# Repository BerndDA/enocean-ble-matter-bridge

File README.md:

# Matter-over-Thread Gateways (BLE, EnOcean and Nuki)

Firmware and hardware for nRF52840 gateways that bring existing devices into a Matter smart home over Thread. There are three separate apps, built from a shared bridge core:

- **BLE gateway** ([firmware/ble-gateway/](firmware/ble-gateway/)): BLE temperature/humidity sensors (BTHome) and eQ-3 radiator thermostats.
- **EnOcean gateway** ([firmware/enocean-gateway/](firmware/enocean-gateway/)): Eltako and D2-01 actuators through a TCM 310/515 module.
- **Nuki gateway** ([firmware/nuki-gateway/](firmware/nuki-gateway/)): a Nuki Smart Lock (3rd/4th generation) over Bluetooth LE, as two Matter door locks: "Front door" and "Door opener".

All are based on the nRF Connect SDK Matter Bridge application (pinned to v3.4.2) and are meant for home use, not certification.

**Documentation is in the [wiki](https://github.com/BerndDA/enocean-ble-matter-bridge/wiki)**:

- [Ready-made firmware](https://github.com/BerndDA/enocean-ble-matter-bridge/wiki/Ready-Made-Firmware) and [commissioning](https://github.com/BerndDA/enocean-ble-matter-bridge/wiki/Commissioning)
- [BLE gateway](https://github.com/BerndDA/enocean-ble-matter-bridge/wiki/BLE-Gateway), [EnOcean gateway](https://github.com/BerndDA/enocean-ble-matter-bridge/wiki/EnOcean-Gateway) and its [commands](https://github.com/BerndDA/enocean-ble-matter-bridge/wiki/EnOcean-Gateway-Commands), [Nuki gateway](https://github.com/BerndDA/enocean-ble-matter-bridge/wiki/Nuki-Gateway)
- Hardware: [boards](https://github.com/BerndDA/enocean-ble-matter-bridge/wiki/Boards), [EnMT carrier board](https://github.com/BerndDA/enocean-ble-matter-bridge/wiki/EnMT-Carrier-Board), [EnOcean bridge PCB](https://github.com/BerndDA/enocean-ble-matter-bridge/wiki/EnOcean-Bridge-PCB), [bootloader](https://github.com/BerndDA/enocean-ble-matter-bridge/wiki/Bootloader)
- Development: [toolchain setup](https://github.com/BerndDA/enocean-ble-matter-bridge/wiki/Toolchain-Setup), [building and flashing](https://github.com/BerndDA/enocean-ble-matter-bridge/wiki/Building-and-Flashing), [repository layout](https://github.com/BerndDA/enocean-ble-matter-bridge/wiki/Repository-Layout), [measurements](https://github.com/BerndDA/enocean-ble-matter-bridge/wiki/Measurements)

Quick start on an nRF52840 DK with the SDK installed:

```sh
make flash                         # BLE gateway; APP=enocean-gateway or APP=nuki-gateway for the others
make identity                      # the board's Matter setup code
```

`make` lists all targets. Open tasks are in [TODO.md](TODO.md).

The wiki is also a git submodule in [wiki/](wiki/): `git submodule update --init wiki` checks it out for editing next to the code. Commit and push page changes inside `wiki/` (that publishes them), then commit the new `wiki` pointer here; `git submodule update --remote wiki` fetches edits made in the browser.

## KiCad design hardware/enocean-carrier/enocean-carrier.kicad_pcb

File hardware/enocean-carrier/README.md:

# EnOcean carrier board (EnMT)

A Pro Micro nRF52840 (nice!nano) on a 2-layer carrier with a TCM 515, hand-soldered.

KiCad project, fabrication files (`fab/`), 3D-printed case (`case/`) and the generator scripts (`tools/`). Design, decisions, ordering and bring-up are on the wiki page [EnMT Carrier Board](https://github.com/BerndDA/enocean-ble-matter-bridge/wiki/EnMT-Carrier-Board).

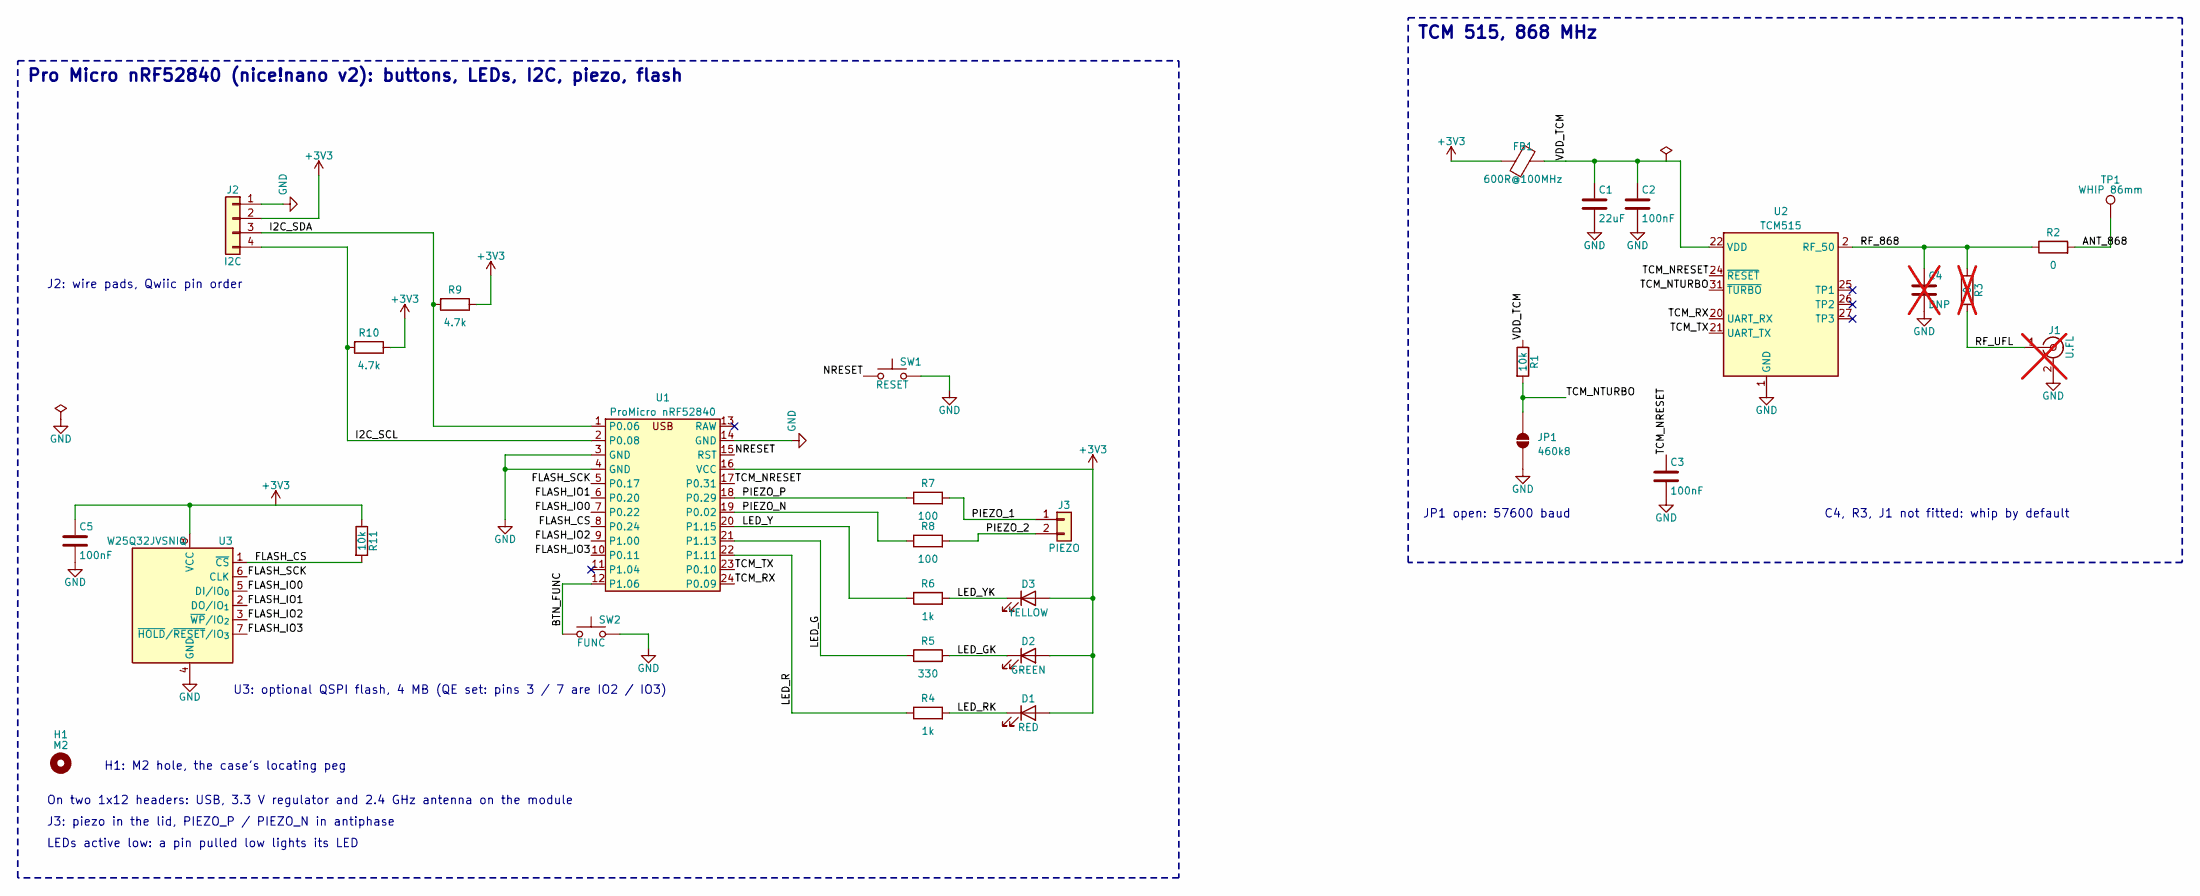
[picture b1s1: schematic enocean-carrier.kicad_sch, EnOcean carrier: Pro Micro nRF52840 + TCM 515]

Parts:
C1: 22uF; C_0805_2012Metric_Pad1.18x1.45mm_HandSolder; MPN CL21A226MAQNNNE; LCSC C45783
C2, C3: 100nF; C_0805_2012Metric_Pad1.18x1.45mm_HandSolder; MPN CC0805KRX7R9BB104; LCSC C49678
C4: DNP; C_0805_2012Metric_Pad1.18x1.45mm_HandSolder; not fitted
C5: 100nF; C_0603_1608Metric_Pad1.08x0.95mm_HandSolder; MPN CC0603KRX7R9BB104; LCSC C14663
D1: RED; LED_0805_2012Metric; MPN NCD0805R1; LCSC C84256
D2: GREEN; LED_0805_2012Metric; MPN KT-0805G; LCSC C2297
D3: YELLOW; LED_0805_2012Metric; MPN KT-0805Y; LCSC C2296
FB1: 600R@100MHz; L_0805_2012Metric_Pad1.05x1.20mm_HandSolder; MPN GZ2012D601TF; LCSC C1017
H1: M2; MountingHole_2.2mm_M2
J1: U.FL; U.FL_Hirose_U.FL-R-SMT-1_Vertical; MPN U.FL-R-SMT-1(80); LCSC C88374; not fitted
J2: I2C; WirePads_1x04_P2.54mm_Drill0.9mm
J3: PIEZO; WirePads_1x02_P2.54mm_Drill0.9mm
JP1: 460k8; SolderJumper-2_P1.3mm_Open_RoundedPad1.0x1.5mm
R1: 10k; R_0805_2012Metric_Pad1.20x1.40mm_HandSolder; MPN 0805W8F1002T5E; LCSC C17414
R2: 0; R_0805_2012Metric_Pad1.20x1.40mm_HandSolder; MPN 0805W8F0000T5E; LCSC C17477
R3: 0; R_0805_2012Metric_Pad1.20x1.40mm_HandSolder; MPN 0805W8F0000T5E; LCSC C17477; not fitted
R4, R6: 1k; R_0603_1608Metric_Pad0.98x0.95mm_HandSolder; MPN 0603WAF1001T5E; LCSC C21190
R5: 330; R_0603_1608Metric_Pad0.98x0.95mm_HandSolder; MPN 0603WAF3300T5E; LCSC C23138
R7, R8: 100; R_0603_1608Metric_Pad0.98x0.95mm_HandSolder; MPN 0603WAF1000T5E; LCSC C22775
R9, R10: 4.7k; R_0603_1608Metric_Pad0.98x0.95mm_HandSolder; MPN 0603WAF4701T5E; LCSC C23162
R11: 10k; R_0603_1608Metric_Pad0.98x0.95mm_HandSolder; MPN 0603WAF1002T5E; LCSC C25804
SW1: RESET; SW_Push_1P1T_XKB_TS-1187A; MPN TS-1187A-B-A-B; LCSC C318884
SW2: FUNC; SW_Push_1P1T_XKB_TS-1187A; MPN TS-1187A-B-A-B; LCSC C318884
TP1: WHIP 86mm; WhipPad_D3.2mm_Drill1.8mm
U1: ProMicro nRF52840; ProMicro_nRF52840; MPN nice!nano v2 / SuperMini nRF52840 with 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
U2: TCM515; TCM515_HandSolder; MPN EnOcean TCM 515 (S3003-K515), 868.3 MHz
U3: W25Q32JVSNIQ; SOIC-8_3.9x4.9mm_P1.27mm; MPN W25Q32JVSNIQ; LCSC C5355146

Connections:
+3V3: C5.1, D1.2 (A), D2.2 (A), D3.2 (A), FB1.1, J2.2, R9.1, R10.1, R11.1, U1.16 (VCC), U3.8 (VCC)
/ANT_868: R2.2, TP1.1
/BTN_FUNC: SW2.1, U1.12 (P1.06)
/FLASH_CS: R11.2, U1.8 (P0.24), U3.1 (~CS)
/FLASH_IO0: U1.7 (P0.22), U3.5 (DI/IO_{0})
/FLASH_IO1: U1.6 (P0.20), U3.2 (DO/IO_{1})
/FLASH_IO2: U1.9 (P1.00), U3.3 (~WP/IO_{2})
/FLASH_IO3: U1.10 (P0.11), U3.7 (~HOLD/~RESET/IO_{3})
/FLASH_SCK: U1.5 (P0.17), U3.6 (CLK)
/I2C_SCL: J2.4, R10.2, U1.2 (P0.08)
/I2C_SDA: J2.3, R9.2, U1.1 (P0.06)
/LED_G: R5.1, U1.21 (P1.13)
/LED_GK: D2.1 (K), R5.2
/LED_R: R4.1, U1.22 (P1.11)
/LED_RK: D1.1 (K), R4.2
/LED_Y: R6.1, U1.20 (P1.15)
/LED_YK: D3.1 (K), R6.2
/NRESET: SW1.1, U1.15 (RST)
/PIEZO_1: J3.1, R7.2
/PIEZO_2: J3.2, R8.2
/PIEZO_N: R8.1, U1.19 (P0.02)
/PIEZO_P: R7.1, U1.18 (P0.29)
/RF_868: C4.1, R2.1, R3.1, U2.2 (RF_50)
/RF_UFL: J1.1 (In), R3.2
/TCM_NRESET: C3.1, U1.17 (P0.31), U2.24 (~RESET)
/TCM_NTURBO: JP1.1 (A), R1.2, U2.31 (~TURBO)
/TCM_RX: U1.24 (P0.09), U2.20 (UART_RX)
/TCM_TX: U1.23 (P0.10), U2.21 (UART_TX)
/VDD_TCM: C1.1, C2.1, FB1.2, R1.1, U2.22 (VDD)
GND: C1.2, C2.2, C3.2, C4.2, C5.2, J1.2 (Ext), J2.1, JP1.2 (B), SW1.2, SW2.2, U1.3 (GND), U1.4 (GND), U1.14 (GND), U2.1 (GND), U2.3 (GND), U2.6 (GND), U2.15 (GND), U2.23 (GND), U3.4 (GND)

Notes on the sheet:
Pro Micro nRF52840 (nice!nano v2): buttons, LEDs, I2C, piezo, flash
TCM 515, 868 MHz
J2: wire pads, Qwiic pin order
On two 1x12 headers: USB, 3.3 V regulator and 2.4 GHz antenna on the module
U3: optional QSPI flash, 4 MB (QE set: pins 3 / 7 are IO2 / IO3)
H1: M2 hole, the case's locating peg
J3: piezo in the lid, PIEZO_P / PIEZO_N in antiphase
LEDs active low: a pin pulled low lights its LED
JP1 open: 57600 baud
C4, R3, J1 not fitted: whip by default

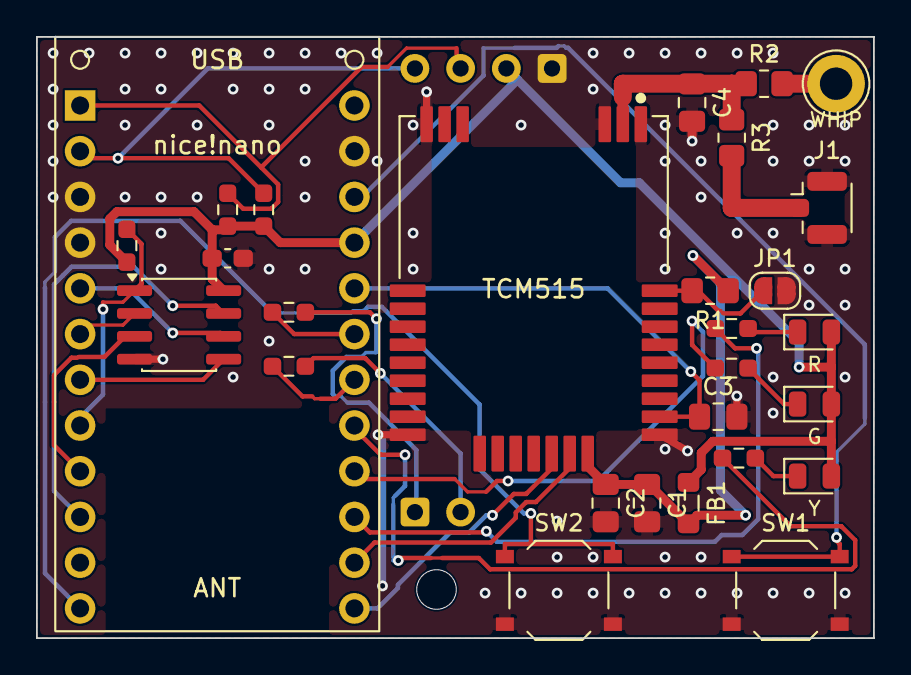
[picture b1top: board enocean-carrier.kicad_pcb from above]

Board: 2 copper layers, 46.5 x 33.4 mm, 31 parts (0 on the bottom side), 30 nets.

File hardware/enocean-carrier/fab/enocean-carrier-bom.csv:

Comment,Designator,Footprint,LCSC Part #
600R@100MHz,FB1,L_0805_2012Metric_Pad1.05x1.20mm_HandSolder,C1017
100nF,C5,C_0603_1608Metric_Pad1.08x0.95mm_HandSolder,C14663
10k,R1,R_0805_2012Metric_Pad1.20x1.40mm_HandSolder,C17414
0,R2,R_0805_2012Metric_Pad1.20x1.40mm_HandSolder,C17477
1k,"R4,R6",R_0603_1608Metric_Pad0.98x0.95mm_HandSolder,C21190
100,"R7,R8",R_0603_1608Metric_Pad0.98x0.95mm_HandSolder,C22775
YELLOW,D3,LED_0805_2012Metric,C2296
GREEN,D2,LED_0805_2012Metric,C2297
330,R5,R_0603_1608Metric_Pad0.98x0.95mm_HandSolder,C23138
4.7k,"R10,R9",R_0603_1608Metric_Pad0.98x0.95mm_HandSolder,C23162
10k,R11,R_0603_1608Metric_Pad0.98x0.95mm_HandSolder,C25804
RESET/FUNC,"SW1,SW2",SW_Push_1P1T_XKB_TS-1187A,C318884
22uF,C1,C_0805_2012Metric_Pad1.18x1.45mm_HandSolder,C45783
100nF,"C2,C3",C_0805_2012Metric_Pad1.18x1.45mm_HandSolder,C49678
W25Q32JVSNIQ,U3,SOIC-8_3.9x4.9mm_P1.27mm,C5355146
RED,D1,LED_0805_2012Metric,C84256

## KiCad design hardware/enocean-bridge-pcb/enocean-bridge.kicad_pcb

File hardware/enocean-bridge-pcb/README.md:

# EnOcean–Matter bridge PCB

One board for the EnOcean gateway: a bare nRF52840, a TCM 515 and USB-C, pin-compatible with the Pro Micro build.

KiCad project, fabrication files (`fab/`), 3D-printed case (`case/`) and the generator scripts (`tools/`). Design, decisions, ordering and bring-up are on the wiki page [EnOcean Bridge PCB](https://github.com/BerndDA/enocean-ble-matter-bridge/wiki/EnOcean-Bridge-PCB).

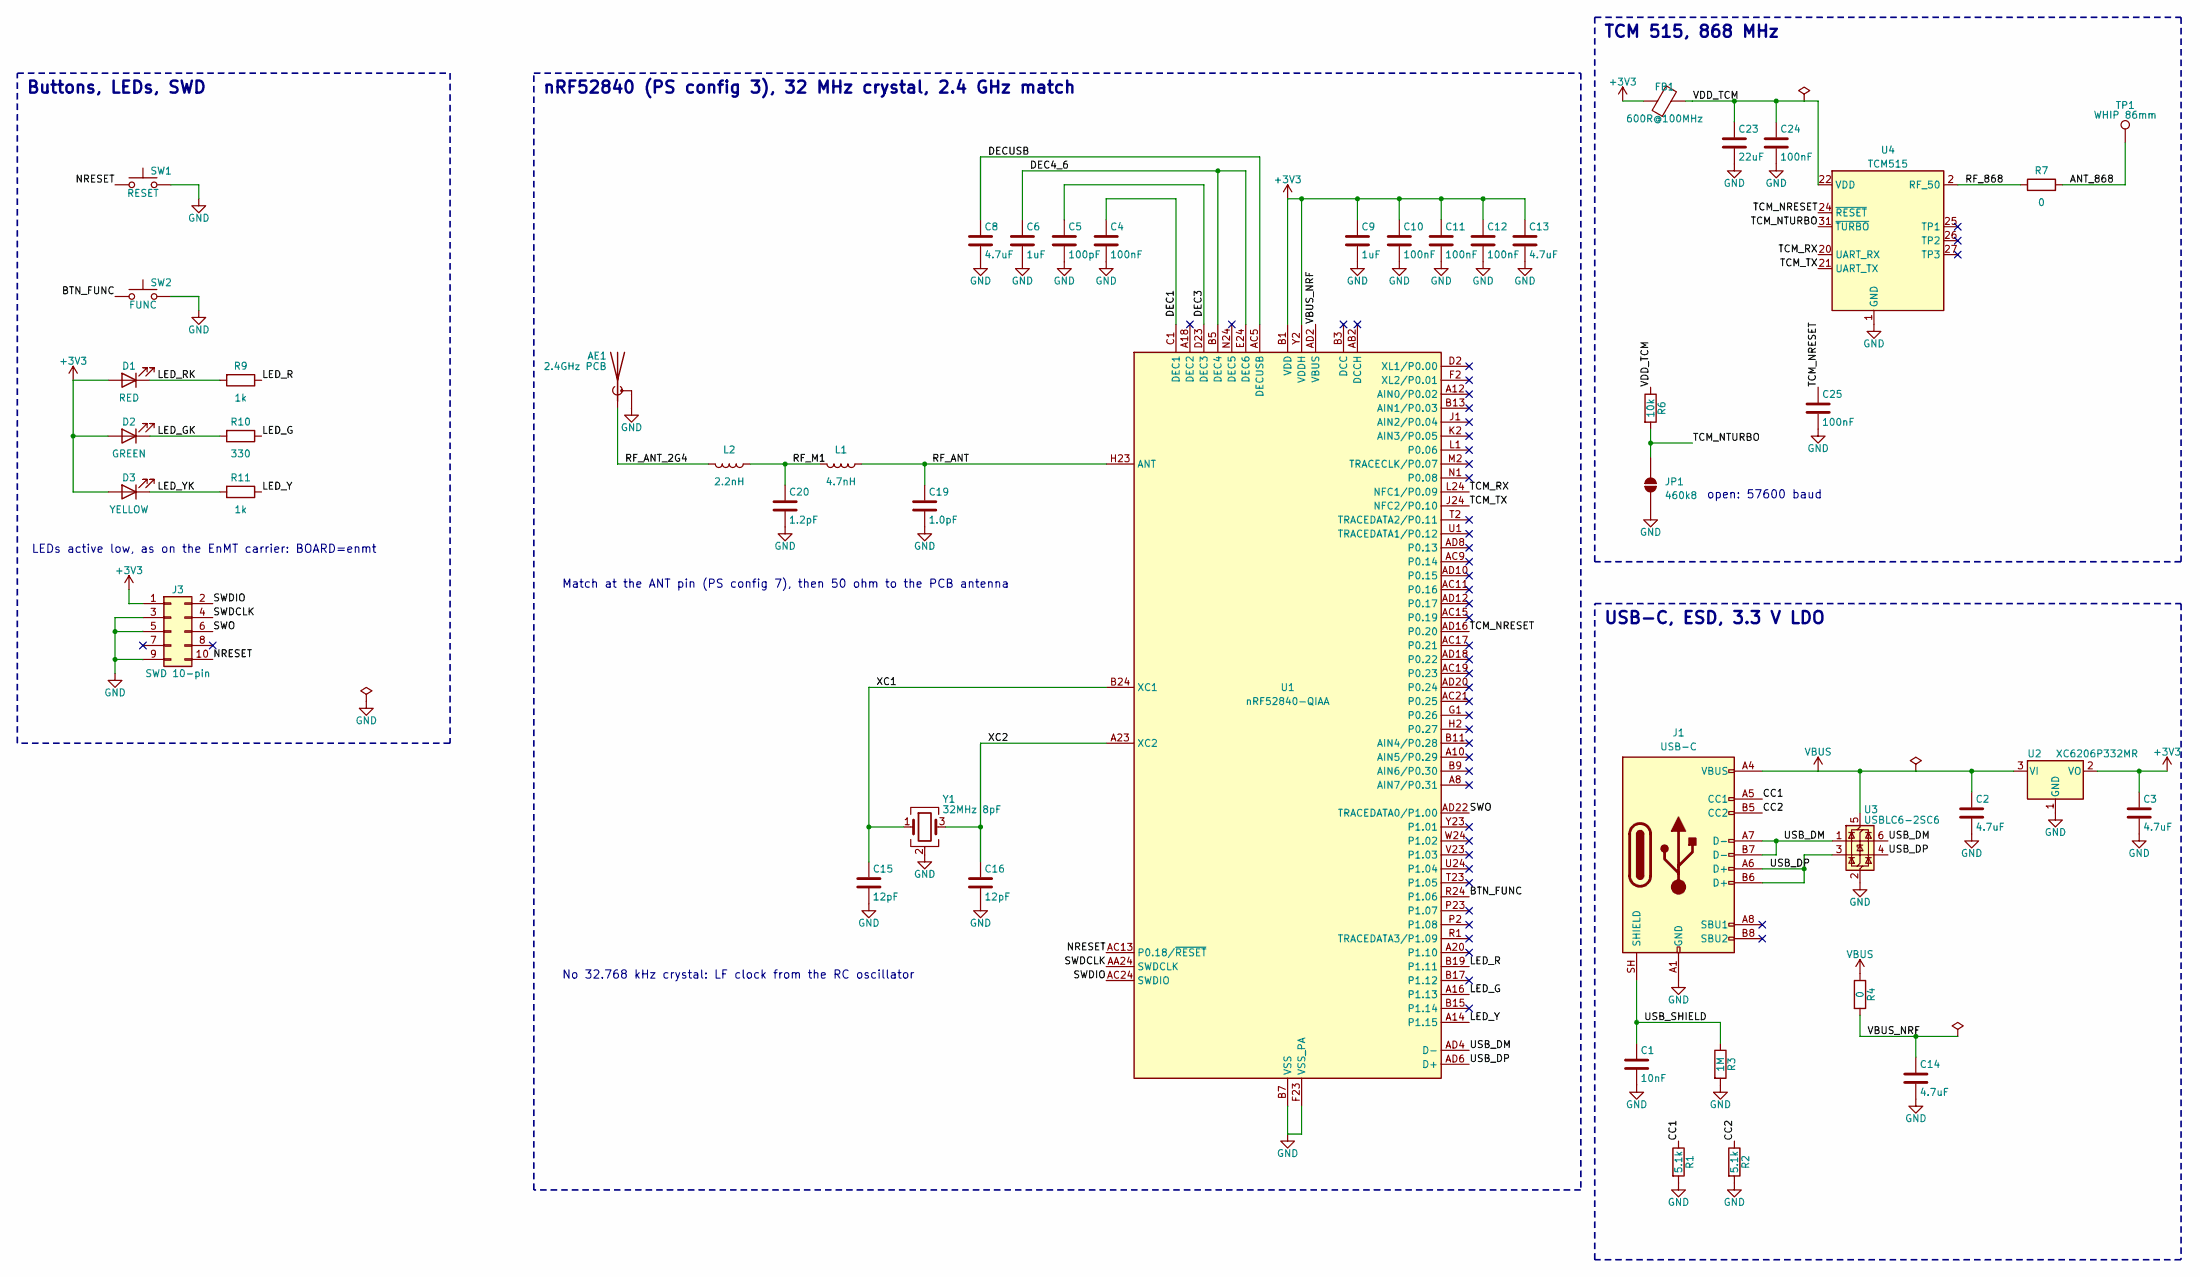
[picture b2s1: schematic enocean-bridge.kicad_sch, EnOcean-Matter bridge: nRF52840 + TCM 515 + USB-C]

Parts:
AE1: 2.4GHz PCB; Texas_SWRA117D_2.4GHz_Left
C1: 10nF; C_0402_1005Metric; MPN CL05B103KB5NNNC; LCSC C15195
C2, C3, C8, C13, C14: 4.7uF; C_0603_1608Metric; MPN CL10A475KO8NNNC; LCSC C19666
C4, C10, C11, C12, C24, C25: 100nF; C_0402_1005Metric; MPN CL05B104KO5NNNC; LCSC C1525
C5: 100pF; C_0402_1005Metric; MPN 0402CG101J500NT; LCSC C1546
C6, C9: 1uF; C_0603_1608Metric; MPN CL10A105KB8NNNC; LCSC C15849
C15, C16: 12pF; C_0402_1005Metric; MPN 0402CG120J500NT; LCSC C1547
C19: 1.0pF; C_0402_1005Metric; MPN GJM1555C1H1R0WB01D; LCSC C72134
C20: 1.2pF; C_0402_1005Metric; MPN GJM1555C1H1R2CB01D; LCSC C85877
C23: 22uF; C_0805_2012Metric; MPN CL21A226MAQNNNE; LCSC C45783
D1: RED; LED_0805_2012Metric; MPN NCD0805R1; LCSC C84256
D2: GREEN; LED_0805_2012Metric; MPN KT-0805G; LCSC C2297
D3: YELLOW; LED_0805_2012Metric; MPN KT-0805Y; LCSC C2296
FB1: 600R@100MHz; L_0603_1608Metric; MPN 742863160 or eq.; LCSC C1002
J1: USB-C; USB_C_Receptacle_HRO_TYPE-C-31-M-12; MPN HRO TYPE-C-31-M-12; LCSC C165948
J3: SWD 10-pin; PinHeader_2x05_P1.27mm_Vertical
JP1: 460k8; SolderJumper-2_P1.3mm_Open_RoundedPad1.0x1.5mm
L1: 4.7nH; L_0402_1005Metric; MPN LQG15HN4N7S02D; LCSC C97989
L2: 2.2nH; L_0402_1005Metric; MPN LQG15HS2N2B02D; LCSC C162540
R1, R2: 5.1k; R_0402_1005Metric; MPN 0402WGF5101TCE; LCSC C25905
R3: 1M; R_0402_1005Metric; MPN 0402WGF1004TCE; LCSC C26083
R4, R7: 0; R_0402_1005Metric; MPN 0402WGF0000TCE; LCSC C17168
R6: 10k; R_0402_1005Metric; MPN 0402WGF1002TCE; LCSC C25744
R9, R11: 1k; R_0603_1608Metric; MPN 0603WAF1001T5E; LCSC C21190
R10: 330; R_0603_1608Metric; MPN 0603WAF3300T5E; LCSC C23138
SW1: RESET; SW_Push_1P1T_XKB_TS-1187A; MPN TS-1187A-B-A-B; LCSC C318884
SW2: FUNC; SW_Push_1P1T_XKB_TS-1187A; MPN TS-1187A-B-A-B; LCSC C318884
TP1: WHIP 86mm; TestPoint_THTPad_D2.0mm_Drill1.0mm
U1: nRF52840-QIAA; Nordic_AQFN-73-1EP_7x7mm_P0.5mm; MPN NRF52840-QIAA-F-R7; LCSC C3606858
U2: XC6206P332MR; SOT-23-3; MPN XC6206P332MR-G; LCSC C5446
U3: USBLC6-2SC6; SOT-23-6; MPN USBLC6-2SC6; LCSC C3029034
U4: TCM515; MPN TCM 515 (hand-solder, not at JLC)
Y1: 32MHz 8pF; Crystal_SMD_2016-4Pin_2.0x1.6mm; MPN ABM11W-32.0000MHZ-8-D1X-T3; LCSC C5189005

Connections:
+3V3: C3.1, C9.1, C10.1, C11.1, C12.1, C13.1, D1.2 (A), D2.2 (A), D3.2 (A), FB1.1, J3.1, U1.A22 (VDD), U1.AD14 (VDD), U1.AD23 (VDD), U1.B1 (VDD), U1.W1 (VDD), U1.Y2 (VDDH), U2.2 (VO)
/ANT_868: R7.2, TP1.1
/BTN_FUNC: SW2.1, U1.R24 (P1.06)
/CC1: J1.A5 (CC1), R1.1
/CC2: J1.B5 (CC2), R2.1
/DEC1: C4.1, U1.C1 (DEC1)
/DEC3: C5.1, U1.D23 (DEC3)
/DEC4_6: C6.1, U1.B5 (DEC4), U1.E24 (DEC6)
/DECUSB: C8.1, U1.AC5 (DECUSB)
/LED_G: R10.1, U1.A16 (P1.13)
/LED_GK: D2.1 (K), R10.2
/LED_R: R9.1, U1.B19 (P1.11)
/LED_RK: D1.1 (K), R9.2
/LED_Y: R11.1, U1.A14 (P1.15)
/LED_YK: D3.1 (K), R11.2
/NRESET: J3.10, SW1.1, U1.AC13 (P0.18/~RESET)
/RF_868: R7.1, U4.2 (RF_50)
/RF_ANT: C19.1, L1.1, U1.H23 (ANT)
/RF_ANT_2G4: AE1.1 (A), L2.2
/RF_M1: C20.1, L1.2, L2.1
/SWDCLK: J3.4, U1.AA24 (SWDCLK)
/SWDIO: J3.2, U1.AC24 (SWDIO)
/SWO: J3.6, U1.AD22 (TRACEDATA0/P1.00)
/TCM_NRESET: C25.1, U1.AD16 (P0.20), U4.24 (~RESET)
/TCM_NTURBO: JP1.1 (A), R6.2, U4.31 (~TURBO)
/TCM_RX: U1.L24 (NFC1/P0.09), U4.20 (UART_RX)
/TCM_TX: U1.J24 (NFC2/P0.10), U4.21 (UART_TX)
/USB_DM: J1.A7 (D-), J1.B7 (D-), U1.AD4 (D-), U3.1 (I/O1), U3.6 (I/O1)
/USB_DP: J1.A6 (D+), J1.B6 (D+), U1.AD6 (D+), U3.3 (I/O2), U3.4 (I/O2)
/USB_SHIELD: C1.1, J1.SH (SHIELD), R3.1
/VBUS_NRF: C14.1, R4.2, U1.AD2 (VBUS)
/VDD_TCM: C23.1, C24.1, FB1.2, R6.1, U4.22 (VDD)
/XC1: C15.1, U1.B24 (XC1), Y1.1
/XC2: C16.1, U1.A23 (XC2), Y1.3
GND: AE1.2 (Shield), C1.2, C2.2, C3.2, C4.2, C5.2, C6.2, C8.2, C9.2, C10.2, C11.2, C12.2, C13.2, C14.2, C15.2, C16.2, C19.2, C20.2, C23.2, C24.2, C25.2, J1.A1 (GND), J1.A12 (GND), J1.B1 (GND), J1.B12 (GND), J3.3, J3.5, J3.9, JP1.2 (B), R1.2, R2.2, R3.2, SW1.2, SW2.2, U1.B7 (VSS), U1.EP (VSS), U1.F23 (VSS_PA), U2.1 (GND), U3.2 (GND), U4.1 (GND), U4.3 (GND), U4.6 (GND), U4.15 (GND), U4.23 (GND), Y1.2 (G), Y1.4 (G)
VBUS: C2.1, J1.A4 (VBUS), J1.A9 (VBUS), J1.B4 (VBUS), J1.B9 (VBUS), R4.1, U2.3 (VI), U3.5 (VBUS)

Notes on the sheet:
Buttons, LEDs, SWD
nRF52840 (PS config 3), 32 MHz crystal, 2.4 GHz match
TCM 515, 868 MHz
USB-C, ESD, 3.3 V LDO
LEDs active low, as on the EnMT carrier: BOARD=enmt
Match at the ANT pin (PS config 7), then 50 ohm to the PCB antenna
No 32.768 kHz crystal: LF clock from the RC oscillator
open: 57600 baud

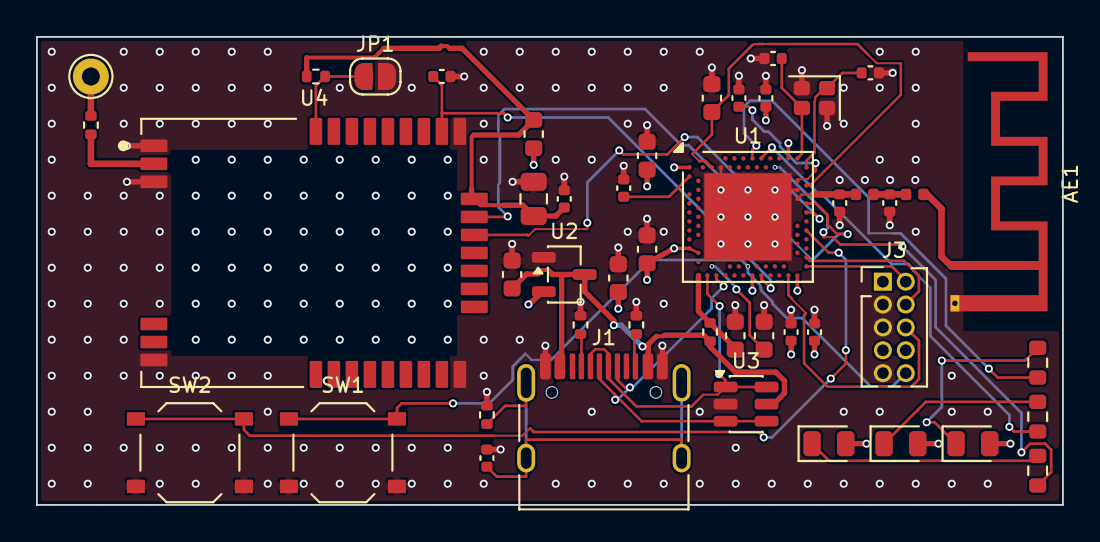
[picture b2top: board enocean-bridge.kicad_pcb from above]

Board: 4 copper layers, 57.0 x 26.0 mm, 47 parts (0 on the bottom side), 36 nets.

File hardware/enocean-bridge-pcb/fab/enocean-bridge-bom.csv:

Comment,Designator,Footprint,LCSC Part #
600R@100MHz,FB1,L_0603_1608Metric,C1002
10nF,C1,C_0402_1005Metric,C15195
100nF,"C10,C11,C12,C24,C25,C4",C_0402_1005Metric,C1525
100pF,C5,C_0402_1005Metric,C1546
12pF,"C15,C16",C_0402_1005Metric,C1547
1uF,"C6,C9",C_0603_1608Metric,C15849
2.2nH,L2,L_0402_1005Metric,C162540
USB-C,J1,USB_C_Receptacle_HRO_TYPE-C-31-M-12,C165948
0,"R4,R7",R_0402_1005Metric,C17168
4.7uF,"C13,C14,C2,C3,C8",C_0603_1608Metric,C19666
1k,"R11,R9",R_0603_1608Metric,C21190
YELLOW,D3,LED_0805_2012Metric,C2296
GREEN,D2,LED_0805_2012Metric,C2297
330,R10,R_0603_1608Metric,C23138
10k,R6,R_0402_1005Metric,C25744
5.1k,"R1,R2",R_0402_1005Metric,C25905
1M,R3,R_0402_1005Metric,C26083
USBLC6-2SC6,U3,SOT-23-6,C3029034
RESET/FUNC,"SW1,SW2",SW_Push_1P1T_XKB_TS-1187A,C318884
nRF52840-QIAA,U1,Nordic_AQFN-73-1EP_7x7mm_P0.5mm,C3606858
22uF,C23,C_0805_2012Metric,C45783
32MHz 8pF,Y1,Crystal_SMD_2016-4Pin_2.0x1.6mm,C5189005
XC6206P332MR,U2,SOT-23-3,C5446
1.0pF,C19,C_0402_1005Metric,C72134
RED,D1,LED_0805_2012Metric,C84256
1.2pF,C20,C_0402_1005Metric,C85877
4.7nH,L1,L_0402_1005Metric,C97989
